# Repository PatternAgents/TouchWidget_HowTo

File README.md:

TouchWidget_HowTo
=================

PatternAgents TouchWidget_HowTo - Control your World!

[  
*PatternAgents TouchWidget_HowTo*](http://www.patternagents.com/projects/index.html)

The PatternAgents TouchWidget_HowTo is an example project of how to use the Touch Widget Library for Eagle.

This work is licensed under a Creative Commons Attribution-ShareAlike 4.0 International License
[  
*Licensing CC BY-SA 4.0*](http://creativecommons.org/licenses/by-sa/4.0/)

It may be used for Educational, Personal, or Commercial Use, provided you keep these notices,
attribution, and share-alike. When you apply these licenses to material you create, 
it meets the Freedom Defined definition of a "Free Cultural Work". 
Free cultural works are the ones that can be most readily used, shared, 
and remixed by others, and go furthest toward creating a commons of freely reusable materials.

-------------------------------------------------------------------------------------------

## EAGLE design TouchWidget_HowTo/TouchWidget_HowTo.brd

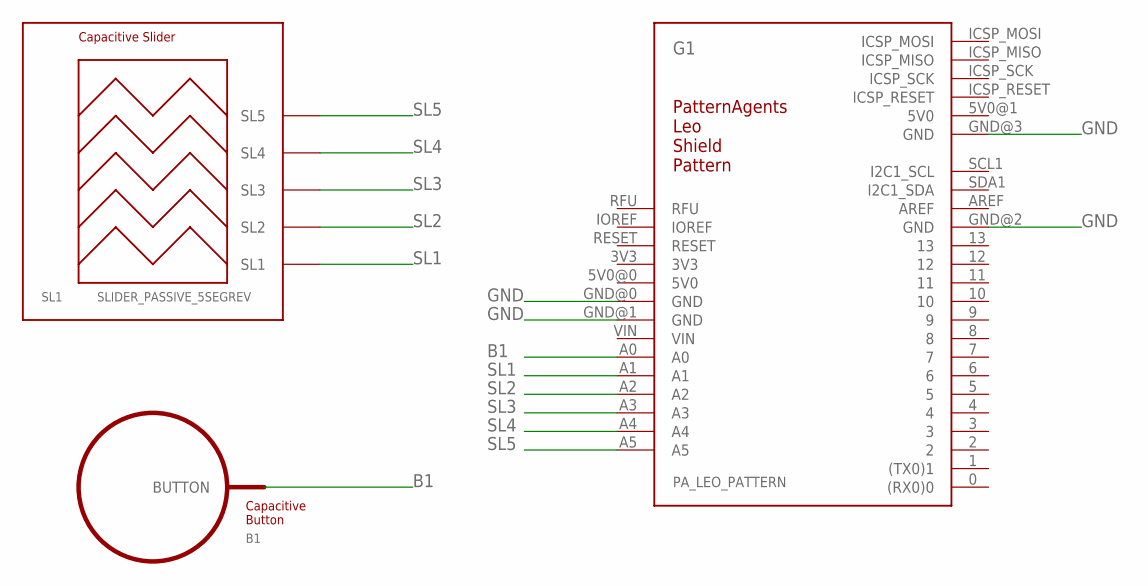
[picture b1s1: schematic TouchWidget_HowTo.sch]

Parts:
B1: BUTTON_PASSIVE10MM; BUTTON_PASSIVE_10MM
G1: PA_LEO_PATTERN
SL1: SLIDER_PASSIVE_5SEGREV; SLIDER_PASSIVE_5SEG_12MM_REV

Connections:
5V0: G1.5V0@1 (5V0)
B1: B1.BUTTON, G1.A0
GND: G1.GND@0 (GND), G1.GND@1 (GND), G1.GND@2 (GND), G1.GND@3 (GND)
RFU: G1.RFU
SL1: G1.A1, SL1.SL1
SL2: G1.A2, SL1.SL2
SL3: G1.A3, SL1.SL3
SL4: G1.A4, SL1.SL4
SL5: G1.A5, SL1.SL5

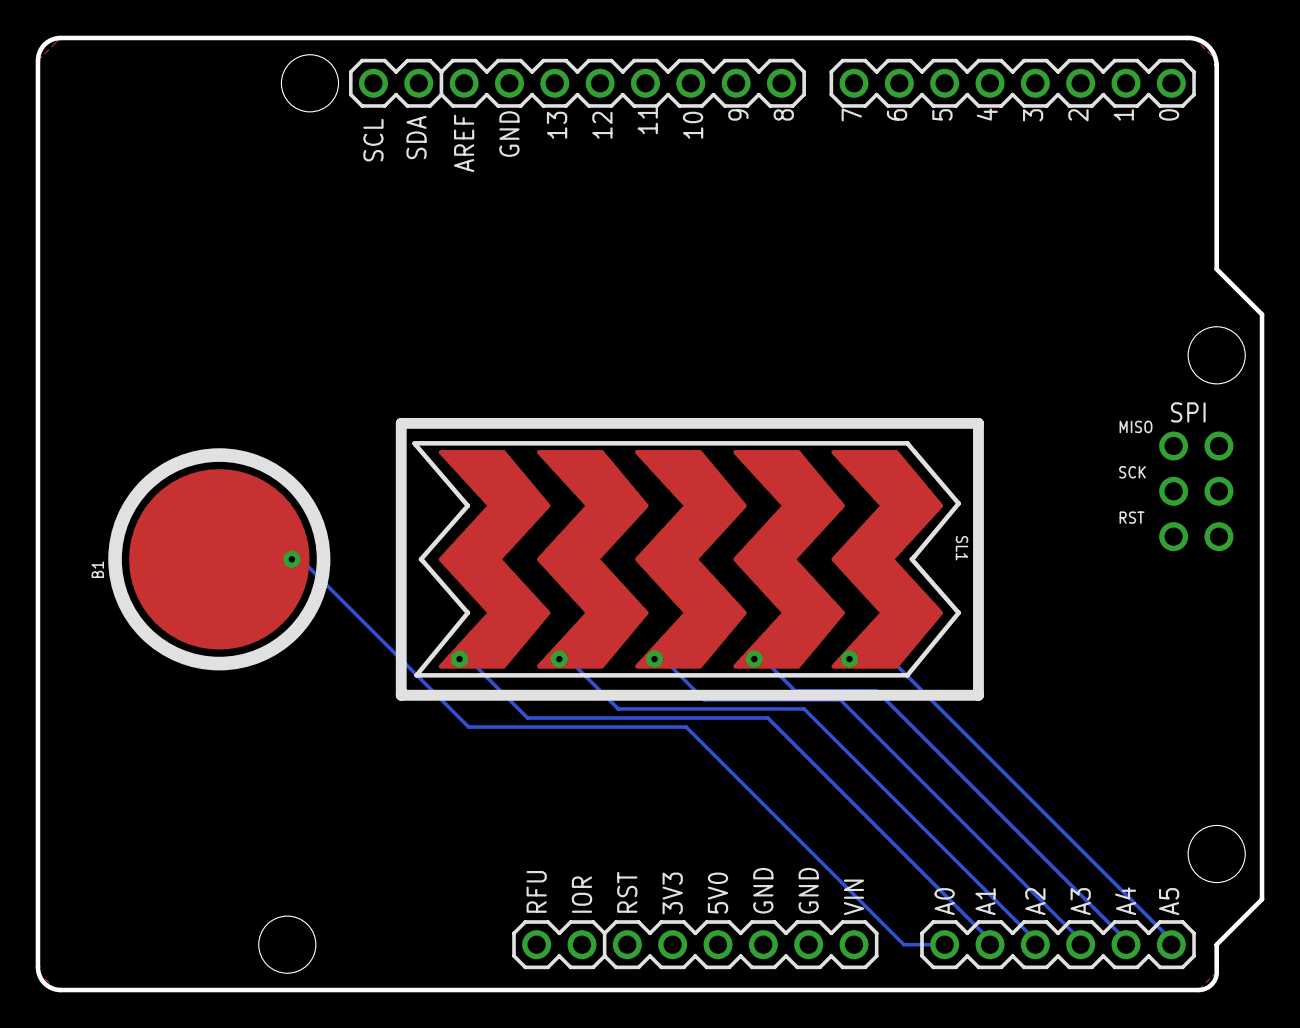
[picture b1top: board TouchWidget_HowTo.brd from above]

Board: 2 copper layers, 68.6 x 53.3 mm, 3 parts (0 on the bottom side), 7 nets.

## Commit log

2013-12-02 Initial Commit
    Update License to CC 4.0
    Add README
    Add Schematic and Layout
2013-12-02 Add Images Directory
2013-12-02 Eagle Files Update
2013-12-23 Move Licensing to CC 4.0 for consistancy

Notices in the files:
parts and their libraries:
PatternAgents-Boards: License : http://creativecommons.org/licenses/by-sa/2.5
(Creative Commons 2.5)
PatternAgents-TouchWidgets: License : http://creativecommons.org/licenses/by-sa/4.0/ (Creative Commons 4.0)
